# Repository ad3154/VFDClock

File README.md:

# VFDClock
A simple vacuum fluorescent display (VFD) tube clock

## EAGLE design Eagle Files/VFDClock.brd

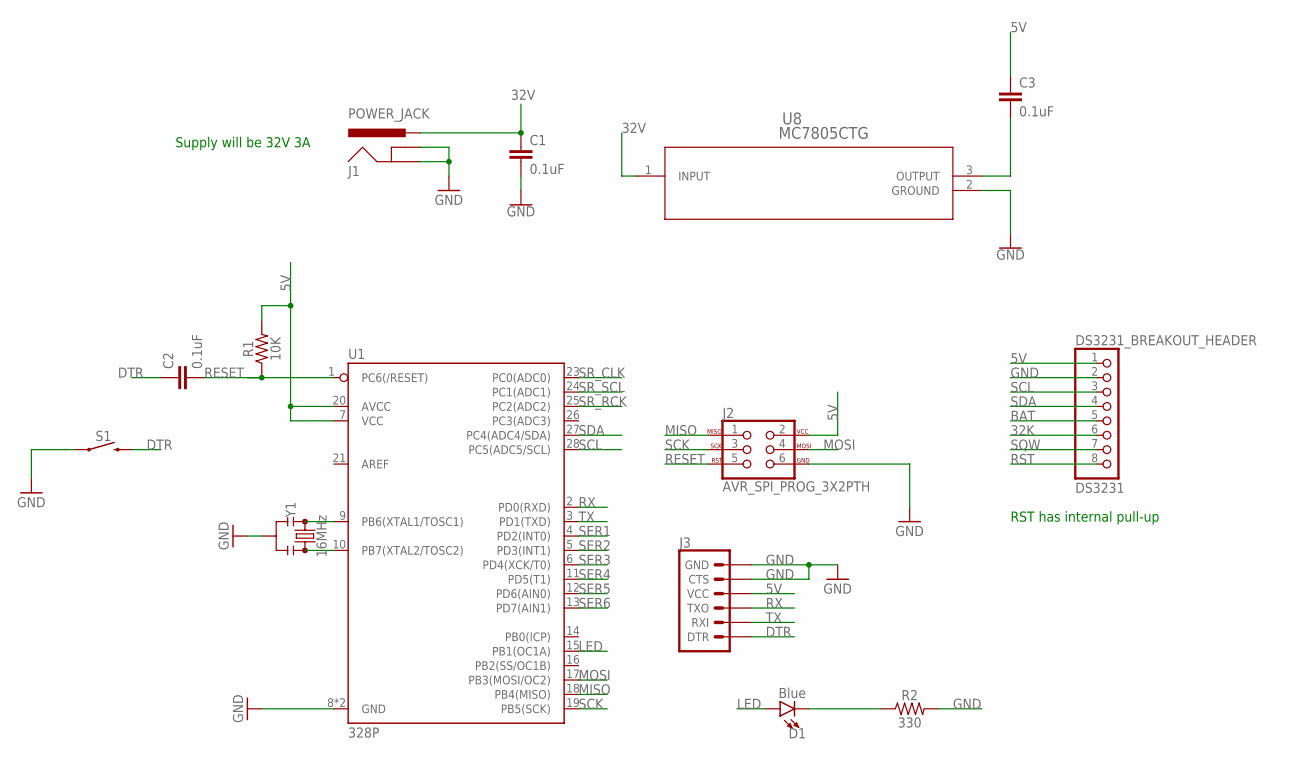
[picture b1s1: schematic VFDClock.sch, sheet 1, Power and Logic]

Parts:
C1, C2: 0.1uF; CAP-PTH-SMALL-KIT
C3: 0.1uF; 0402-CAP
D1: Blue; LED_5MM
DS3231_BREAKOUT_HEADER: DS3231; 1X08_ROUND_70
J1: POWER_JACK; POWER_JACK_PTH
J2: AVR_SPI_PROG_3X2PTH; 2X3
J3: 6_PIN_SERIAL_TARGETLONGPADS; 1X06_LONGPADS
R1: 10K; AXIAL-0.3
R2: 330; AXIAL-0.3
S1: MOMENTARY-SWITCH-SPST-PTH-6.0MM; TACTILE_SWITCH_PTH_6.0MM
U1: 328P; DIP28
U8: MC7805CTG; TO-220AB
Y1: 16MHz; RESONATOR-PTH-7.6X3.8

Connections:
5V: C3.1, DS3231_BREAKOUT_HEADER.1, J2.2, J3.4 (VCC), R1.P$2 (2), U1.7 (VCC), U1.20 (AVCC); also elsewhere on the board
5V_BEFORECAP: C3.2, U8.3 (OUTPUT)
32K: DS3231_BREAKOUT_HEADER.6
32V: C1.1, J1.PWR, U8.1 (INPUT); also elsewhere on the board
BAT: DS3231_BREAKOUT_HEADER.5
DTR: C2.1, J3.1 (DTR), S1.3 (2)
GND: C1.2, DS3231_BREAKOUT_HEADER.2, J1.GND, J1.GNDBREAK, J2.6, J3.5 (CTS), J3.6 (GND), R2.P$2 (2), S1.1, U1.8 (GND), U1.22 (GND), U8.2 (GROUND), Y1.2; also elsewhere on the board
LED: D1.A, U1.15 (PB1(OC1A))
MISO: J2.1, U1.18 (PB4(MISO))
MOSI: J2.4, U1.17 (PB3(MOSI/OC2))
unnamed: U1.9 (PB6(XTAL1/TOSC1)), Y1.1
unnamed: U1.10 (PB7(XTAL2/TOSC2)), Y1.3
unnamed: D1.K (C), R2.P$1 (1)
RESET: C2.2, J2.5, R1.P$1 (1), U1.1 (PC6(/RESET))
RST: DS3231_BREAKOUT_HEADER.8
RX: J3.3 (TXO), U1.2 (PD0(RXD))
SCK: J2.3, U1.19 (PB5(SCK))
SCL: DS3231_BREAKOUT_HEADER.3, U1.28 (PC5(ADC5/SCL))
SDA: DS3231_BREAKOUT_HEADER.4, U1.27 (PC4(ADC4/SDA))
SER1: U1.4 (PD2(INT0)); also elsewhere on the board
SER2: U1.5 (PD3(INT1)); also elsewhere on the board
SER3: U1.6 (PD4(XCK/T0)); also elsewhere on the board
SER4: U1.11 (PD5(T1)); also elsewhere on the board
SER5: U1.12 (PD6(AIN0)); also elsewhere on the board
SER6: U1.13 (PD7(AIN1)); also elsewhere on the board
SQW: DS3231_BREAKOUT_HEADER.7
SR_CLK: U1.23 (PC0(ADC0)); also elsewhere on the board
SR_RCK: U1.25 (PC2(ADC2)); also elsewhere on the board
SR_SCL: U1.24 (PC1(ADC1)); also elsewhere on the board
TX: J3.2 (RXI), U1.3 (PD1(TXD))

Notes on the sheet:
RST has internal pull-up
Supply will be 32V 3A

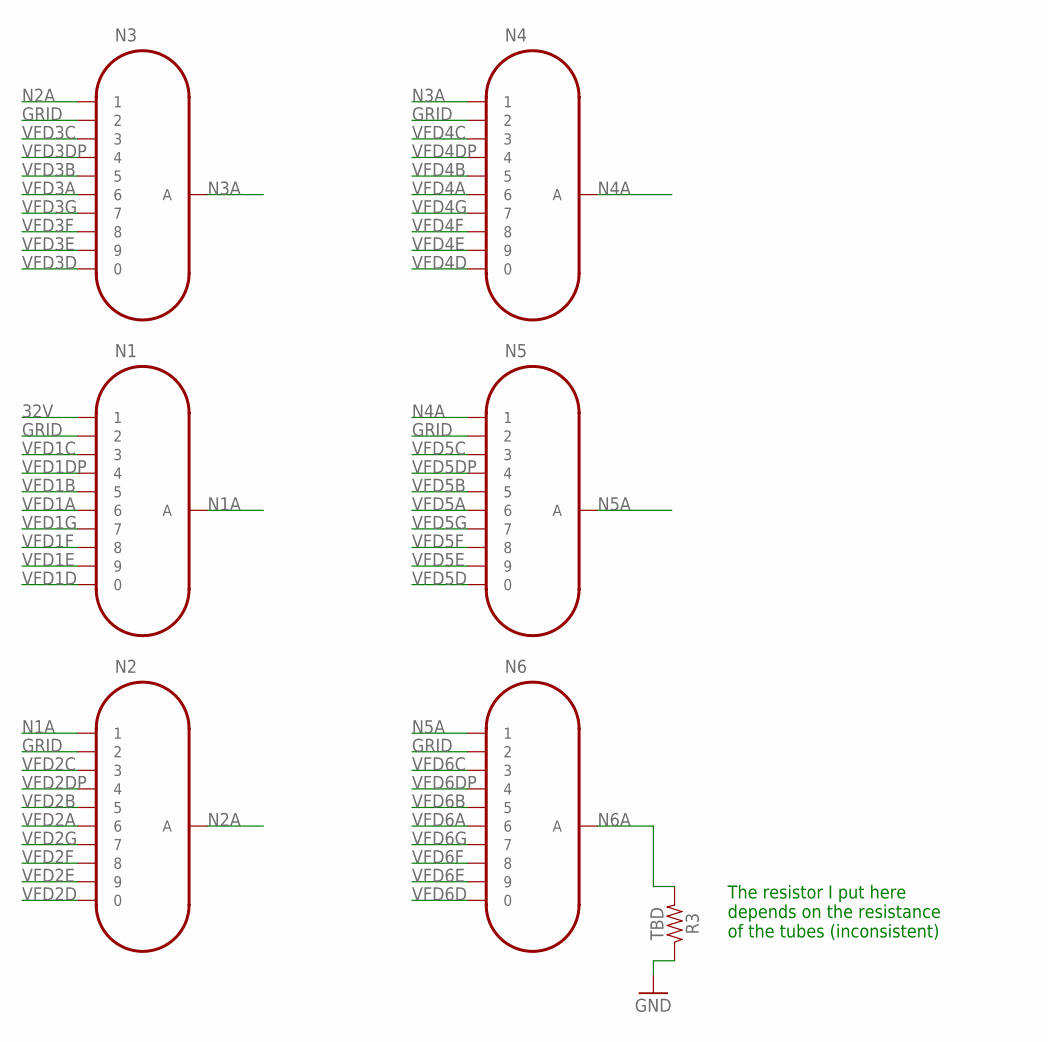
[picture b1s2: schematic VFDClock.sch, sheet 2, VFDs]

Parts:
N1, N2, N3, N4, N5, N6: IN-8
R3: TBD; AXIAL-0.3

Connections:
32V: N1.1; also elsewhere on the board
GND: R3.P$1 (1); also elsewhere on the board
GRID: N1.2, N2.2, N3.2, N4.2, N5.2, N6.2
N1A: N1.A, N2.1
N2A: N2.A, N3.1
N3A: N3.A, N4.1
N4A: N4.A, N5.1
N5A: N5.A, N6.1
N6A: N6.A, R3.P$2 (2)
VFD1A: N1.6; also elsewhere on the board
VFD1B: N1.5; also elsewhere on the board
VFD1C: N1.3; also elsewhere on the board
VFD1D: N1.0; also elsewhere on the board
VFD1DP: N1.4; also elsewhere on the board
VFD1E: N1.9; also elsewhere on the board
VFD1F: N1.8; also elsewhere on the board
VFD1G: N1.7; also elsewhere on the board
VFD2A: N2.6; also elsewhere on the board
VFD2B: N2.5; also elsewhere on the board
VFD2C: N2.3; also elsewhere on the board
VFD2D: N2.0; also elsewhere on the board
VFD2DP: N2.4; also elsewhere on the board
VFD2E: N2.9; also elsewhere on the board
VFD2F: N2.8; also elsewhere on the board
VFD2G: N2.7; also elsewhere on the board
VFD3A: N3.6; also elsewhere on the board
VFD3B: N3.5; also elsewhere on the board
VFD3C: N3.3; also elsewhere on the board
VFD3D: N3.0; also elsewhere on the board
VFD3DP: N3.4; also elsewhere on the board
VFD3E: N3.9; also elsewhere on the board
VFD3F: N3.8; also elsewhere on the board
VFD3G: N3.7; also elsewhere on the board
VFD4A: N4.6; also elsewhere on the board
VFD4B: N4.5; also elsewhere on the board
VFD4C: N4.3; also elsewhere on the board
VFD4D: N4.0; also elsewhere on the board
VFD4DP: N4.4; also elsewhere on the board
VFD4E: N4.9; also elsewhere on the board
VFD4F: N4.8; also elsewhere on the board
VFD4G: N4.7; also elsewhere on the board
VFD5A: N5.6; also elsewhere on the board
VFD5B: N5.5; also elsewhere on the board
VFD5C: N5.3; also elsewhere on the board
VFD5D: N5.0; also elsewhere on the board
VFD5DP: N5.4; also elsewhere on the board
VFD5E: N5.9; also elsewhere on the board
VFD5F: N5.8; also elsewhere on the board
VFD5G: N5.7; also elsewhere on the board
VFD6A: N6.6; also elsewhere on the board
VFD6B: N6.5; also elsewhere on the board
VFD6C: N6.3; also elsewhere on the board
VFD6D: N6.0; also elsewhere on the board
VFD6DP: N6.4; also elsewhere on the board
VFD6E: N6.9; also elsewhere on the board
VFD6F: N6.8; also elsewhere on the board
VFD6G: N6.7; also elsewhere on the board

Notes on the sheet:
The resistor I put here depends on the resistance of the tubes (inconsistent)

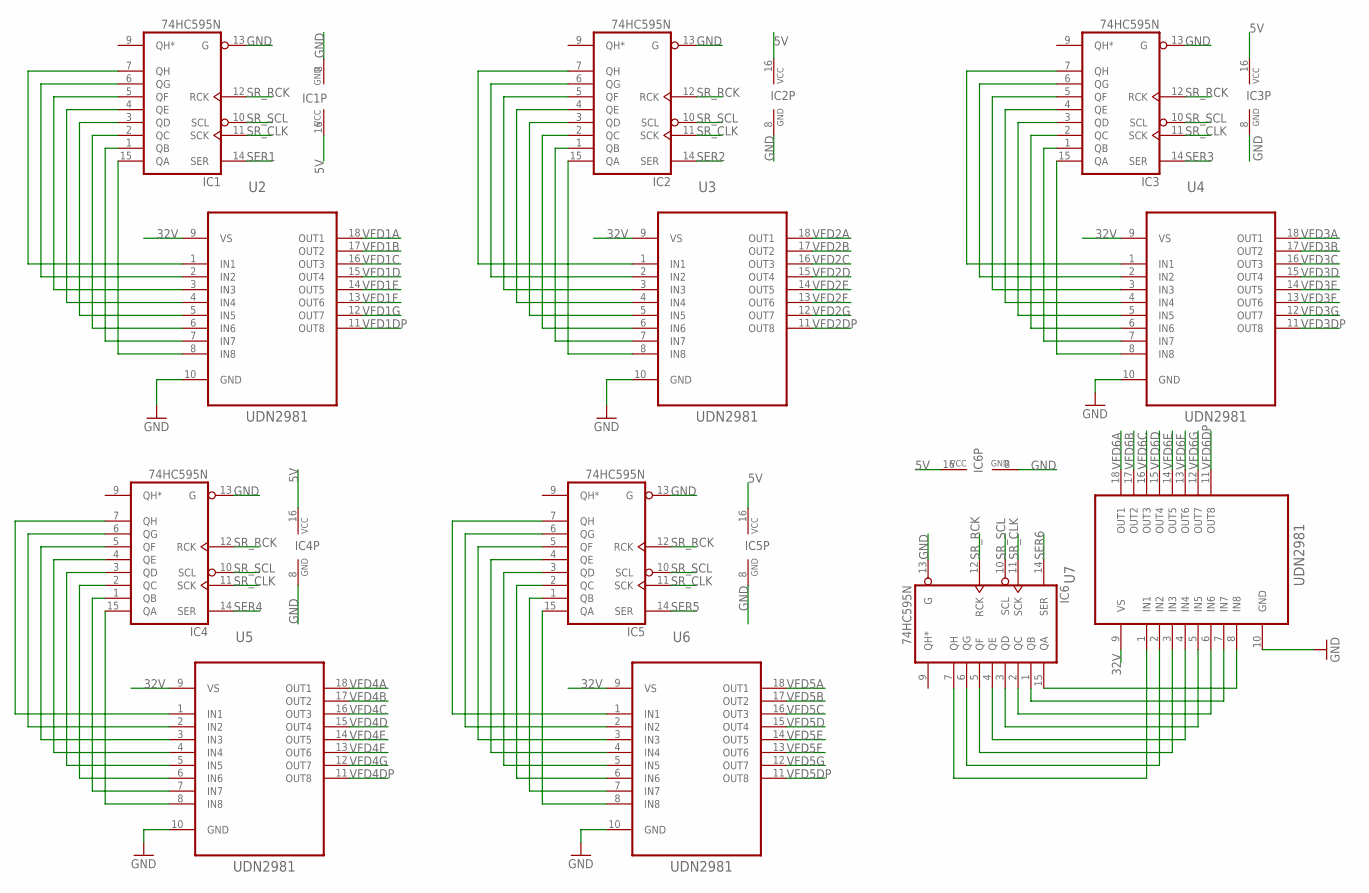
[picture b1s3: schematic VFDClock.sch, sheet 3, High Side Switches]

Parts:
IC1, IC2, IC3, IC4, IC5, IC6: 74HC595N; DIL16
U2, U3, U4, U5, U6, U7: UDN2981; DIP254P762X533-18

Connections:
5V: IC1.16 (VCC), IC2.16 (VCC), IC3.16 (VCC), IC4.16 (VCC), IC5.16 (VCC), IC6.16 (VCC); also elsewhere on the board
32V: U2.9 (VS), U3.9 (VS), U4.9 (VS), U5.9 (VS), U6.9 (VS), U7.9 (VS); also elsewhere on the board
GND: IC1.8 (GND), IC1.13 (G), IC2.8 (GND), IC2.13 (G), IC3.8 (GND), IC3.13 (G), IC4.8 (GND), IC4.13 (G), IC5.8 (GND), IC5.13 (G), IC6.8 (GND), IC6.13 (G), U2.10 (GND), U3.10 (GND), U4.10 (GND), U5.10 (GND), U6.10 (GND), U7.10 (GND); also elsewhere on the board
unnamed: IC1.7 (QH), U2.1 (IN1)
unnamed: IC1.6 (QG), U2.2 (IN2)
unnamed: IC1.3 (QD), U2.5 (IN5)
unnamed: IC1.5 (QF), U2.3 (IN3)
unnamed: IC1.4 (QE), U2.4 (IN4)
unnamed: IC1.2 (QC), U2.6 (IN6)
unnamed: IC1.1 (QB), U2.7 (IN7)
unnamed: IC1.15 (QA), U2.8 (IN8)
unnamed: IC2.7 (QH), U3.1 (IN1)
unnamed: IC2.6 (QG), U3.2 (IN2)
unnamed: IC2.5 (QF), U3.3 (IN3)
unnamed: IC2.4 (QE), U3.4 (IN4)
unnamed: IC2.3 (QD), U3.5 (IN5)
unnamed: IC2.2 (QC), U3.6 (IN6)
unnamed: IC2.1 (QB), U3.7 (IN7)
unnamed: IC2.15 (QA), U3.8 (IN8)
unnamed: IC3.7 (QH), U4.1 (IN1)
unnamed: IC3.6 (QG), U4.2 (IN2)
unnamed: IC3.5 (QF), U4.3 (IN3)
unnamed: IC3.4 (QE), U4.4 (IN4)
unnamed: IC3.3 (QD), U4.5 (IN5)
unnamed: IC3.2 (QC), U4.6 (IN6)
unnamed: IC3.1 (QB), U4.7 (IN7)
unnamed: IC3.15 (QA), U4.8 (IN8)
unnamed: IC4.7 (QH), U5.1 (IN1)
unnamed: IC4.6 (QG), U5.2 (IN2)
unnamed: IC4.5 (QF), U5.3 (IN3)
unnamed: IC4.4 (QE), U5.4 (IN4)
unnamed: IC4.3 (QD), U5.5 (IN5)
unnamed: IC4.2 (QC), U5.6 (IN6)
unnamed: IC4.1 (QB), U5.7 (IN7)
unnamed: IC4.15 (QA), U5.8 (IN8)
unnamed: IC5.7 (QH), U6.1 (IN1)
unnamed: IC5.6 (QG), U6.2 (IN2)
unnamed: IC5.5 (QF), U6.3 (IN3)
unnamed: IC5.4 (QE), U6.4 (IN4)
unnamed: IC5.3 (QD), U6.5 (IN5)
unnamed: IC5.2 (QC), U6.6 (IN6)
unnamed: IC5.1 (QB), U6.7 (IN7)
unnamed: IC5.15 (QA), U6.8 (IN8)
unnamed: IC6.7 (QH), U7.1 (IN1)
unnamed: IC6.6 (QG), U7.2 (IN2)
unnamed: IC6.5 (QF), U7.3 (IN3)
unnamed: IC6.4 (QE), U7.4 (IN4)
unnamed: IC6.3 (QD), U7.5 (IN5)
unnamed: IC6.2 (QC), U7.6 (IN6)
unnamed: IC6.1 (QB), U7.7 (IN7)
unnamed: IC6.15 (QA), U7.8 (IN8)
SER1: IC1.14 (SER); also elsewhere on the board
SER2: IC2.14 (SER); also elsewhere on the board
SER3: IC3.14 (SER); also elsewhere on the board
SER4: IC4.14 (SER); also elsewhere on the board
SER5: IC5.14 (SER); also elsewhere on the board
SER6: IC6.14 (SER); also elsewhere on the board
SR_CLK: IC1.11 (SCK), IC2.11 (SCK), IC3.11 (SCK), IC4.11 (SCK), IC5.11 (SCK), IC6.11 (SCK); also elsewhere on the board
SR_RCK: IC1.12 (RCK), IC2.12 (RCK), IC3.12 (RCK), IC4.12 (RCK), IC5.12 (RCK), IC6.12 (RCK); also elsewhere on the board
SR_SCL: IC1.10 (SCL), IC2.10 (SCL), IC3.10 (SCL), IC4.10 (SCL), IC5.10 (SCL), IC6.10 (SCL); also elsewhere on the board
VFD1A: U2.18 (OUT1); also elsewhere on the board
VFD1B: U2.17 (OUT2); also elsewhere on the board
VFD1C: U2.16 (OUT3); also elsewhere on the board
VFD1D: U2.15 (OUT4); also elsewhere on the board
VFD1DP: U2.11 (OUT8); also elsewhere on the board
VFD1E: U2.14 (OUT5); also elsewhere on the board
VFD1F: U2.13 (OUT6); also elsewhere on the board
VFD1G: U2.12 (OUT7); also elsewhere on the board
VFD2A: U3.18 (OUT1); also elsewhere on the board
VFD2B: U3.17 (OUT2); also elsewhere on the board
VFD2C: U3.16 (OUT3); also elsewhere on the board
VFD2D: U3.15 (OUT4); also elsewhere on the board
VFD2DP: U3.11 (OUT8); also elsewhere on the board
VFD2E: U3.14 (OUT5); also elsewhere on the board
VFD2F: U3.13 (OUT6); also elsewhere on the board
VFD2G: U3.12 (OUT7); also elsewhere on the board
VFD3A: U4.18 (OUT1); also elsewhere on the board
VFD3B: U4.17 (OUT2); also elsewhere on the board
VFD3C: U4.16 (OUT3); also elsewhere on the board
VFD3D: U4.15 (OUT4); also elsewhere on the board
VFD3DP: U4.11 (OUT8); also elsewhere on the board
VFD3E: U4.14 (OUT5); also elsewhere on the board
VFD3F: U4.13 (OUT6); also elsewhere on the board
VFD3G: U4.12 (OUT7); also elsewhere on the board
VFD4A: U5.18 (OUT1); also elsewhere on the board
VFD4B: U5.17 (OUT2); also elsewhere on the board
VFD4C: U5.16 (OUT3); also elsewhere on the board
VFD4D: U5.15 (OUT4); also elsewhere on the board
VFD4DP: U5.11 (OUT8); also elsewhere on the board
VFD4E: U5.14 (OUT5); also elsewhere on the board
VFD4F: U5.13 (OUT6); also elsewhere on the board
VFD4G: U5.12 (OUT7); also elsewhere on the board
VFD5A: U6.18 (OUT1); also elsewhere on the board
VFD5B: U6.17 (OUT2); also elsewhere on the board
VFD5C: U6.16 (OUT3); also elsewhere on the board
VFD5D: U6.15 (OUT4); also elsewhere on the board
VFD5DP: U6.11 (OUT8); also elsewhere on the board
VFD5E: U6.14 (OUT5); also elsewhere on the board
VFD5F: U6.13 (OUT6); also elsewhere on the board
VFD5G: U6.12 (OUT7); also elsewhere on the board
VFD6A: U7.18 (OUT1); also elsewhere on the board
VFD6B: U7.17 (OUT2); also elsewhere on the board
VFD6C: U7.16 (OUT3); also elsewhere on the board
VFD6D: U7.15 (OUT4); also elsewhere on the board
VFD6DP: U7.11 (OUT8); also elsewhere on the board
VFD6E: U7.14 (OUT5); also elsewhere on the board
VFD6F: U7.13 (OUT6); also elsewhere on the board
VFD6G: U7.12 (OUT7); also elsewhere on the board

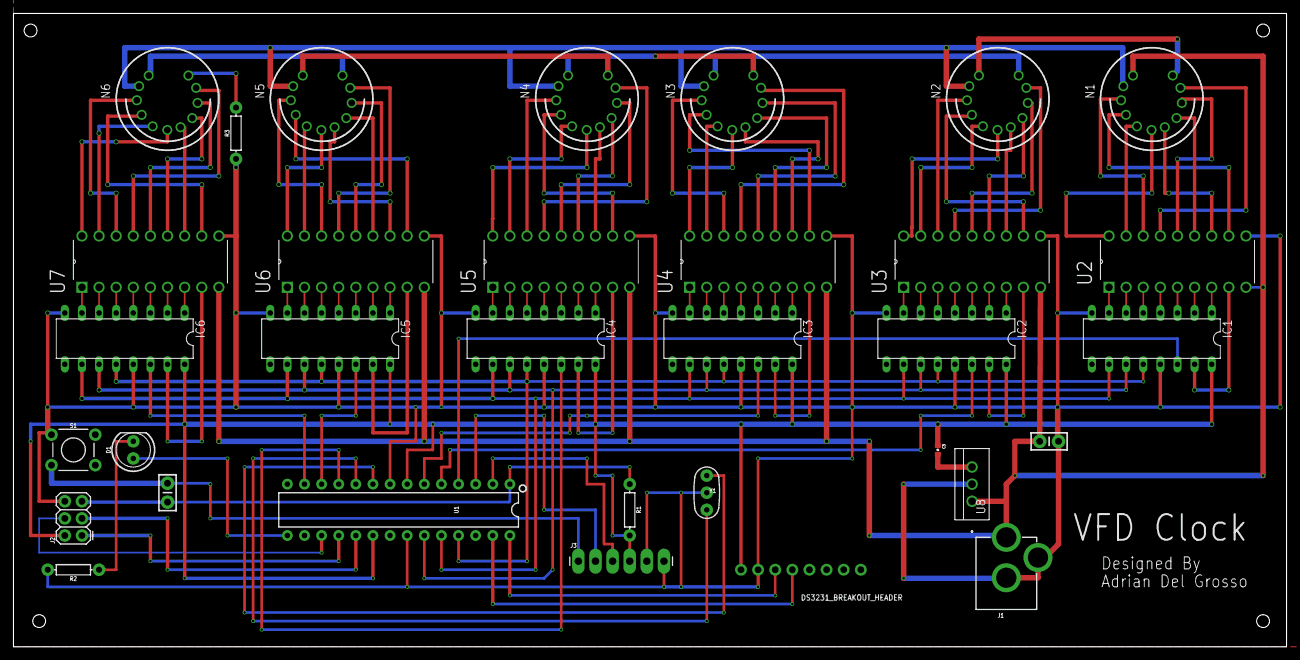
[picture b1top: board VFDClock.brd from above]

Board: 2 copper layers, 188.9 x 94.0 mm, 33 parts (0 on the bottom side), 129 nets.

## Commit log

2019-12-01 Added Eagle files

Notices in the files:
parts and their libraries:
SparkFun-IC-Microcontroller: Licensing: Creative Commons ShareAlike 4.0 International - https://creativecommons.org/licenses/by-sa/4.0
microbuilder: This work is placed in the public domain, and may be freely used for commercial and non-commercial work with the following conditions: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
